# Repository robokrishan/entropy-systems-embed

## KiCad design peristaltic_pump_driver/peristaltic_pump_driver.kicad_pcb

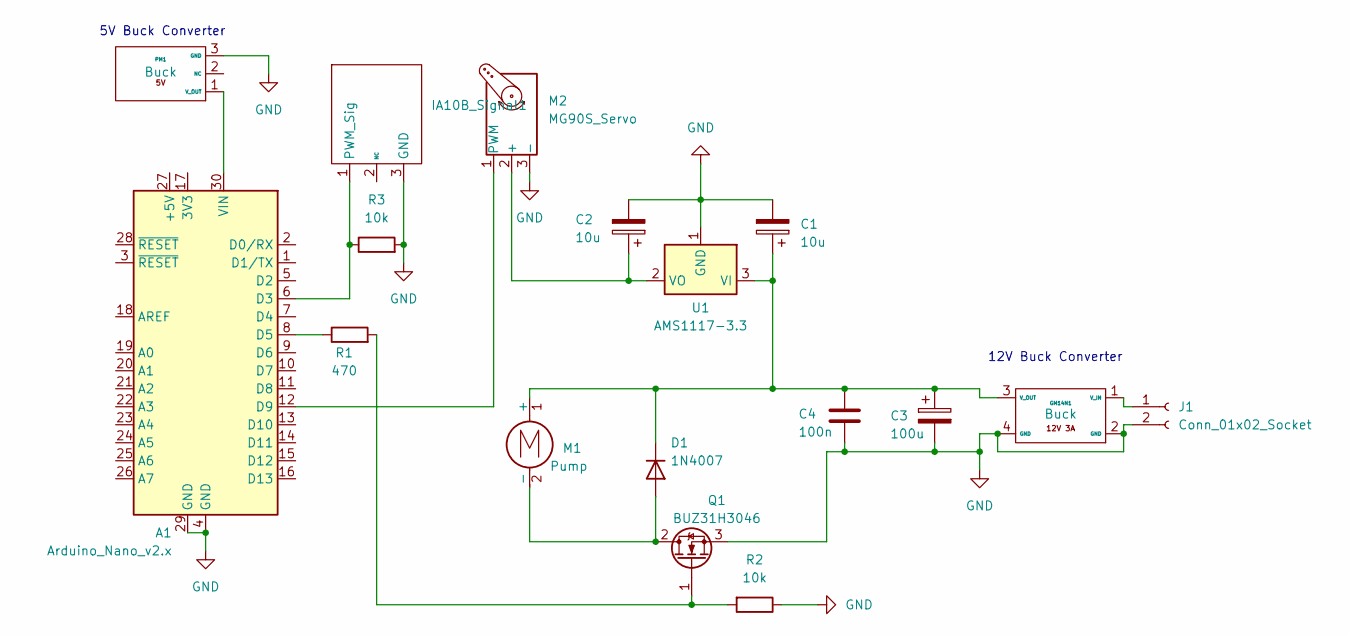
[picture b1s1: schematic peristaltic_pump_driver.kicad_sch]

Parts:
A1: Arduino_Nano_v2.x; Arduino_Nano
C1, C2: 10u; CP_Radial_D4.0mm_P1.50mm
C3: 100u; CP_Radial_D8.0mm_P3.50mm
C4: 100n; C_Disc_D3.0mm_W1.6mm_P2.50mm
D1: 1N4007; D_DO-35_SOD27_P7.62mm_Horizontal
GM14N1: Buck; Untitled_1
IA10B_Signal1: PinHeader_1x03_P2.54mm_Vertical
J1: Conn_01x02_Socket; JST_PH_B2B-PH-K_1x02_P2.00mm_Vertical
M1: Pump; SolderWire-0.25sqmm_1x02_P4.2mm_D0.65mm_OD1.7mm
M2: MG90S_Servo; PinHeader_1x03_P2.54mm_Vertical
PM1: Buck; PinHeader_1x03_P2.54mm_Vertical
Q1: BUZ31H3046; TO-262-3_Vertical
R1: 470; R_Axial_DIN0207_L6.3mm_D2.5mm_P7.62mm_Horizontal
R2, R3: 10k; R_Axial_DIN0207_L6.3mm_D2.5mm_P7.62mm_Horizontal
U1: AMS1117-3.3; SOT-223-3_TabPin2

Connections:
GND: A1.4 (GND), A1.29 (GND), C1.2, C2.2, C3.2, C4.2, GM14N1.2 (GND), GM14N1.4 (GND), IA10B_Signal1.3 (GND), J1.2, M2.3 (-), PM1.3 (GND), Q1.3 (S), R2.1, R3.2, U1.1 (GND)
unnamed: A1.6 (D3), IA10B_Signal1.1 (PWM_Sig), R3.1
unnamed: A1.8 (D5), R1.1
unnamed: A1.12 (D9), M2.1 (PWM)
unnamed: A1.30 (VIN), PM1.1 (V_OUT)
unnamed: D1.2 (A), M1.2 (-), Q1.2 (D)
unnamed: C1.1, C3.1, C4.1, D1.1 (K), GM14N1.3 (V_OUT), M1.1 (+), U1.3 (VI)
unnamed: GM14N1.1 (V_IN), J1.1
unnamed: C2.1, M2.2 (+), U1.2 (VO)
unnamed: Q1.1 (G), R1.2, R2.2

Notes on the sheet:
5V Buck Converter
12V Buck Converter

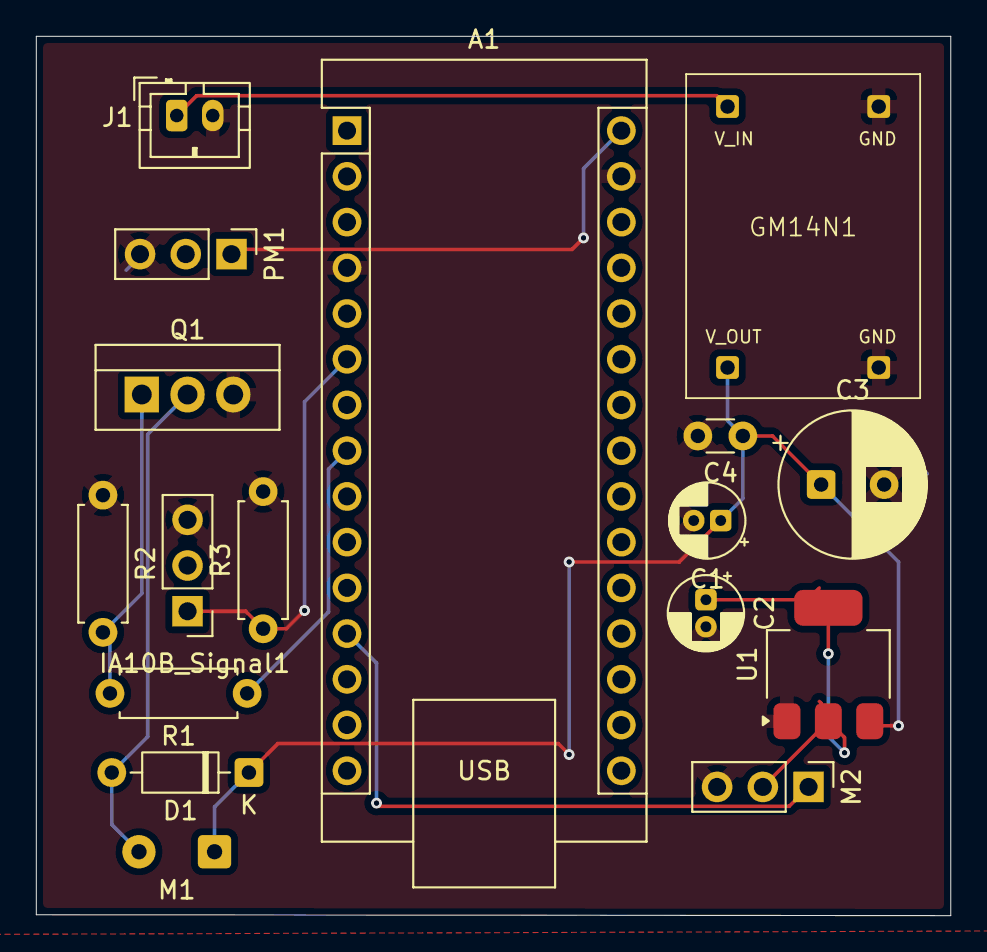
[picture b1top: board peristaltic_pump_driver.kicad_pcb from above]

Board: 4 copper layers, 50.8 x 48.9 mm, 17 parts (0 on the bottom side), 10 nets.
